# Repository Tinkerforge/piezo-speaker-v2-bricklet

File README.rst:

Piezo Speaker Bricklet 2.0
==========================

This repository contains the firmware source code and the hardware design
files. The documentation generator configs can be found at
https://github.com/Tinkerforge/generators

Repository Content
------------------

software/:
 * examples/: Examples for all supported languages
 * build/: Compiled files
 * src/: Source code of firmware
 * Makefile: Makefile to build project

hardware/:
 * Contains KiCad project files and additionally schematics as PDF

datasheets/:
 * Contains datasheets for sensors and complex ICs that are used

Hardware
--------

The hardware is designed with the open source EDA Suite KiCad
(http://www.kicad.org). Before you are able to open the files,
you have to install the Tinkerforge kicad-libraries
(https://github.com/Tinkerforge/kicad-libraries). You can either clone
them directly in hardware/ or clone them in a separate folder and
symlink them into hardware/
(ln -s kicad_path/kicad-libraries project_path/hardware). After that you
can open the .pro file in hardware/ with KiCad and from there view and
modify the schematics and the PCB layout.

Software
--------

If you want to do your own Brick/Bricklet firmware development we highly
recommend that you use our build environment setup script and read the
tutorial (https://www.tinkerforge.com/en/doc/Tutorials/Tutorial_Build_Environment/Tutorial.html).

To compile the C code we recommend you to install the newest GNU Arm Embedded
Toolchain (https://launchpad.net/gcc-arm-embedded/+download).
You also need to install bricklib2 (https://github.com/Tinkerforge/bricklib2).

You can either clone it directly in software/src/ or clone it in a
separate folder and symlink it into software/src/
(ln -s bricklib_path/bricklib2 project_path/software/src/). Finally make sure to
have CMake installed (http://www.cmake.org/cmake/resources/software.html).

After that you can build the firmware by invoking make in software/.
The firmware (.zbin) can then be found in software/build/ and uploaded
with brickv (click button "Flashing" on start screen).

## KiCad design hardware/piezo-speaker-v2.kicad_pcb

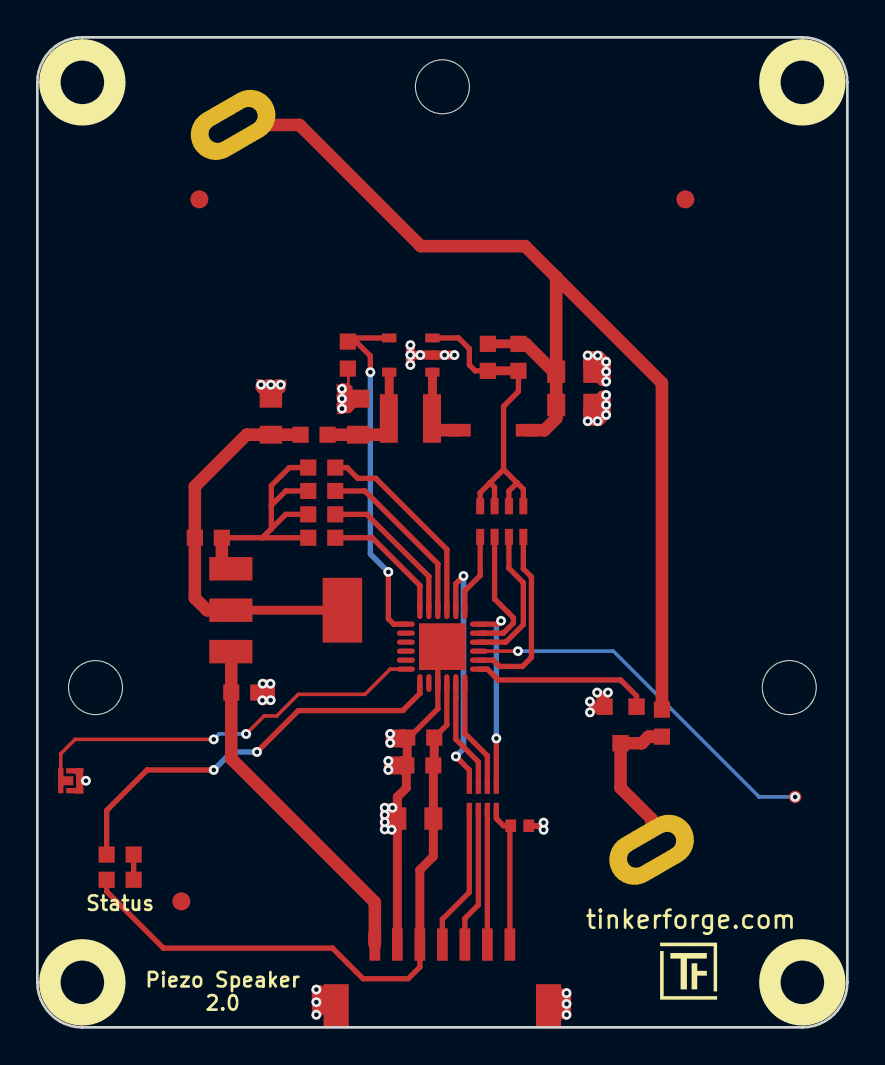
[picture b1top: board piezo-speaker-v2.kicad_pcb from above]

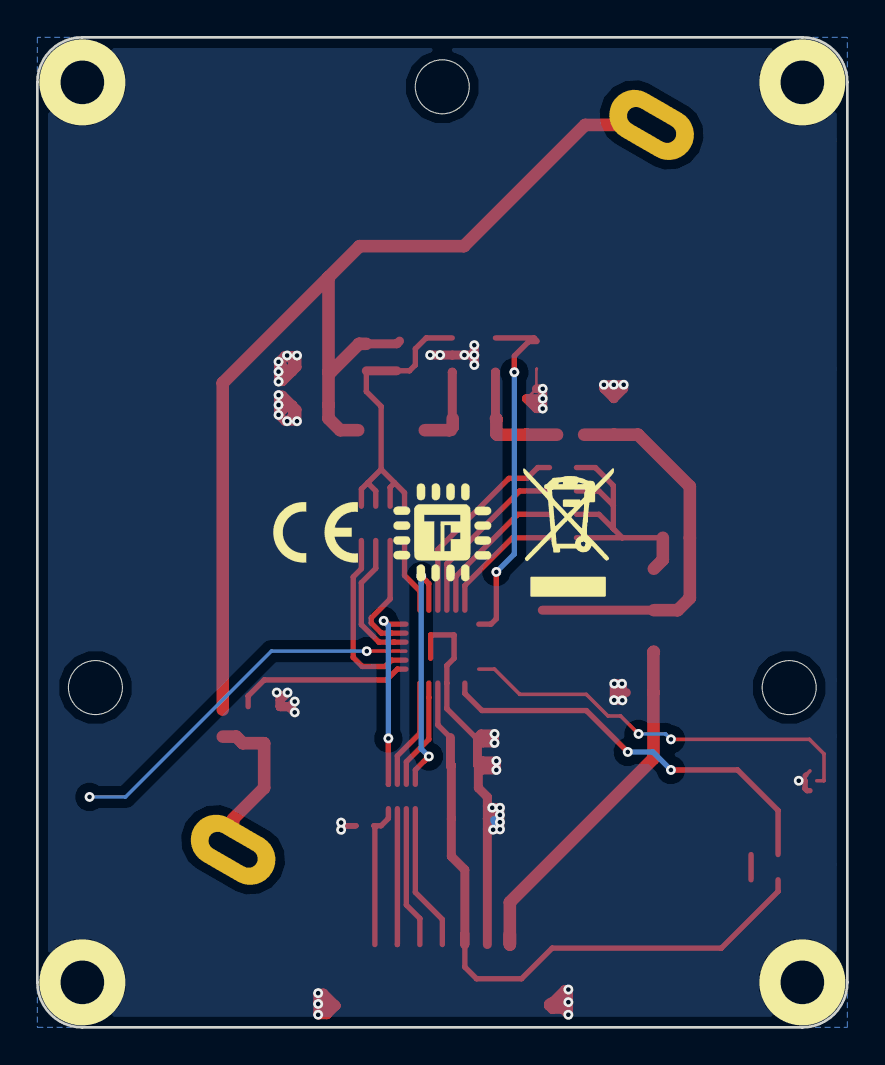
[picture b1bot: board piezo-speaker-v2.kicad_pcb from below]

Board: 2 copper layers, 45.0 x 55.0 mm, 42 parts (2 on the bottom side), 32 nets.

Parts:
C1: 220pF; C0402F
C2: 10uF; C0805
C3, C6: 1uF; C0603F
C4: 100nF; C0603F
C5, C7, C9, C10: 4.7uF; C0805
C8: 270pF; C0603F
D1: blue; D0603F
D3: B0520LW-7-F; SOD-123
Fiducial_Mark: VAL**; Fiducial_Mark
Fiducial_Mark#2, Fiducial_Mark#3: VAL**; Fiducial_Mark
L1: FB; C0603F
L2: 10uH; NR3030
P1: CON-SENSOR2
P2: BOOT; SolderJumper
P3: DEBUG; DEBUG_PAD
P4: PT-4532PLQ
Q101: 2N7002P; SOT23GDS
R1, R2, R101, R102: 1k; R0603F
R3: 330; R0603F
R4: 120k; R0603F
R103: 470; R0603F
R104: 220; R0603F
R105: 100; R0603F
RP1: 82; 4X0402
RP3: 33k; 4X0603
U1: XMC1100; QFN24-4x4mm-0.5mm
U2: LD1117-ADJ; SOT-223
U3: LMR62014X; SOT23-5
U4, U5, U6, U7: DRILL; DRILL_NP
VAL: WEEE_7mm
VAL#2: CE_5mm

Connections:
3V3: C2.1, C3.1, C4.1, D1.1, P1.3, U1.10
+VSW: C6.1, P1.1, U2.3
GND: C1.2, C2.2, C3.2, C4.2, C5.2, C6.2, C7.2, C9.2, C10.2, P1.2, P1.EP, P2.1, Q101.S, R2.2, U1.9, U1.EXP, U3.2
LR-1: R102.2, U1.21
LR-2: R103.2, U1.22
LR-3: R104.2, U1.23
LR-4: R105.2, U1.24
unnamed: C1.1, P1.7, RP1.4
unnamed: C5.1, L1.2, R3.1, U2.2
unnamed: C7.1, L1.1, L2.1, U3.5
unnamed: C8.2, R4.2, RP3.1, RP3.2, RP3.3, RP3.4, U3.3
unnamed: C8.1, C9.1, C10.1, D3.2, P4.1, R4.1, R101.1
unnamed: D1.2, R1.2
unnamed: D3.1, L2.2, U3.1
unnamed: P1.4, RP1.1
unnamed: P1.5, RP1.2
unnamed: P1.6, RP1.3
unnamed: P2.2, U1.6
unnamed: P3.1, U1.15
unnamed: P4.2, Q101.D, R101.2
unnamed: R1.1, U1.7
unnamed: R3.2, R102.1, R103.1, R104.1, R105.1, U2.1
S-CLK: RP1.7, U1.11
S-CS: RP1.8, U1.20
S-MISO: RP1.5, U1.18
S-MOSI: RP1.6, U1.12
SU-1: RP3.5, U1.14
SU-2: RP3.6, U1.16
SU-3: RP3.7, U1.17
SU-4: RP3.8, U1.19
SU-SHDN: R2.1, U1.1, U3.4
Speaker: Q101.G, U1.13

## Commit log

2018-08-29 add symbol table
2018-08-29 created schematics
2018-08-29 created pcb layout
2018-08-29 changed pcb design
2018-08-29 final pcb design (ready for prototype)
2018-09-04 improve some fiducials, add text
2018-09-18 fix outline
2018-09-18 changed the PT footprint, logos, erase and debug pin and first moved the first cap
2018-09-18 changed R4 from 118k to 120k
2018-09-28 Add readme.txt and gitignore
2018-10-04 add hints
2018-10-31 Add initial stub implementation
2018-10-31 Add LMR62014 datasheet
2018-10-31 fix schematic, add 2n7002p, change pins
2018-10-31 fix schematic, pcb not fixed
2018-11-27 change prototype resistor values
2018-11-27 update resistor values
2019-01-22 fix bugs
2019-01-22 drc, change bottom copper plane
2019-02-06 specify rp3 to 33k
2019-02-06 Add minimal implementation that can do simple beep
2019-02-06 Add documentation for volume bitmask
2019-02-13 Implement API
2019-02-14 Rename datasheet
2019-02-14 Fix duration/start time mixup
2019-02-18 Add auto-generated examples
2019-02-21 add fiducial marks
2019-02-22 changed processor to XMC1100
2019-02-26 specify ld1117-adj
2019-04-30 Turn logging off
2019-05-07 Apply bootloader pointer end fix to all new Bricklets
2019-05-09 add schematic
2019-05-10 add cutout information
2019-05-13 add 3d model of speaker
2019-05-13 add 3d data
2019-05-13 fix file names
2019-05-15 add correct drills
2019-05-20 Release Bricklet
2019-05-29 Increase version for new release (changes in bricklib2)
2019-05-29 Add rev to changelog
2019-10-28 Fix copy/paste error in beep duration calculation
    We accidentially used the beep_start bool value instead of
    the beep_start_time
2019-10-28 Increase version to 2.0.2 and add changelog
2019-10-28 Fix copy/paste error in beep duration calculation for alarm too
2019-10-28 Add ref for v2.0.2
2020-01-13 examples: Use python3 input instead of python2 raw_input.
2020-03-16 Whitespace
2020-04-07 examples: rust: Always block when calling bindings functions.
2020-07-23 Add LabVIEW examples
2020-08-19 Add uc examples.
2020-08-25 uc: Fix whitespace
2020-08-27 uc: Fix warnings.
2020-09-02 uc: Add example driver note.
2021-10-25 Update KiCad link
    https://www.kicad.org/blog/2021/10/Avoid-links-to-former-kicad-domain/
2022-04-19 examples: uc: Rename TF_HalContext to TF_HAL.
2022-04-27 uc: Adapt to bindings changes
2022-07-06 Add license files.
2025-10-04 Fix compatibility with new Docker build image (GCC 14.2.1)

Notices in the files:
hardware/piezo-speaker-v2.kicad_pcb:
Copyright Tinkerforge GmbH 2018.
This documentation describes Open Hardware and is licensed under the
CERN OHL v. 1.1.
